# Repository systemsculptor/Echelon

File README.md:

# risc-v-research

### Features
Modularity, Ports, Periperials will be able to be swapped out. 

Cost efficient solution for students or professionals looking for a laptop 

Reparibility is very straightforward and simple. 

Upgradability is supported for these devices for lifetime.

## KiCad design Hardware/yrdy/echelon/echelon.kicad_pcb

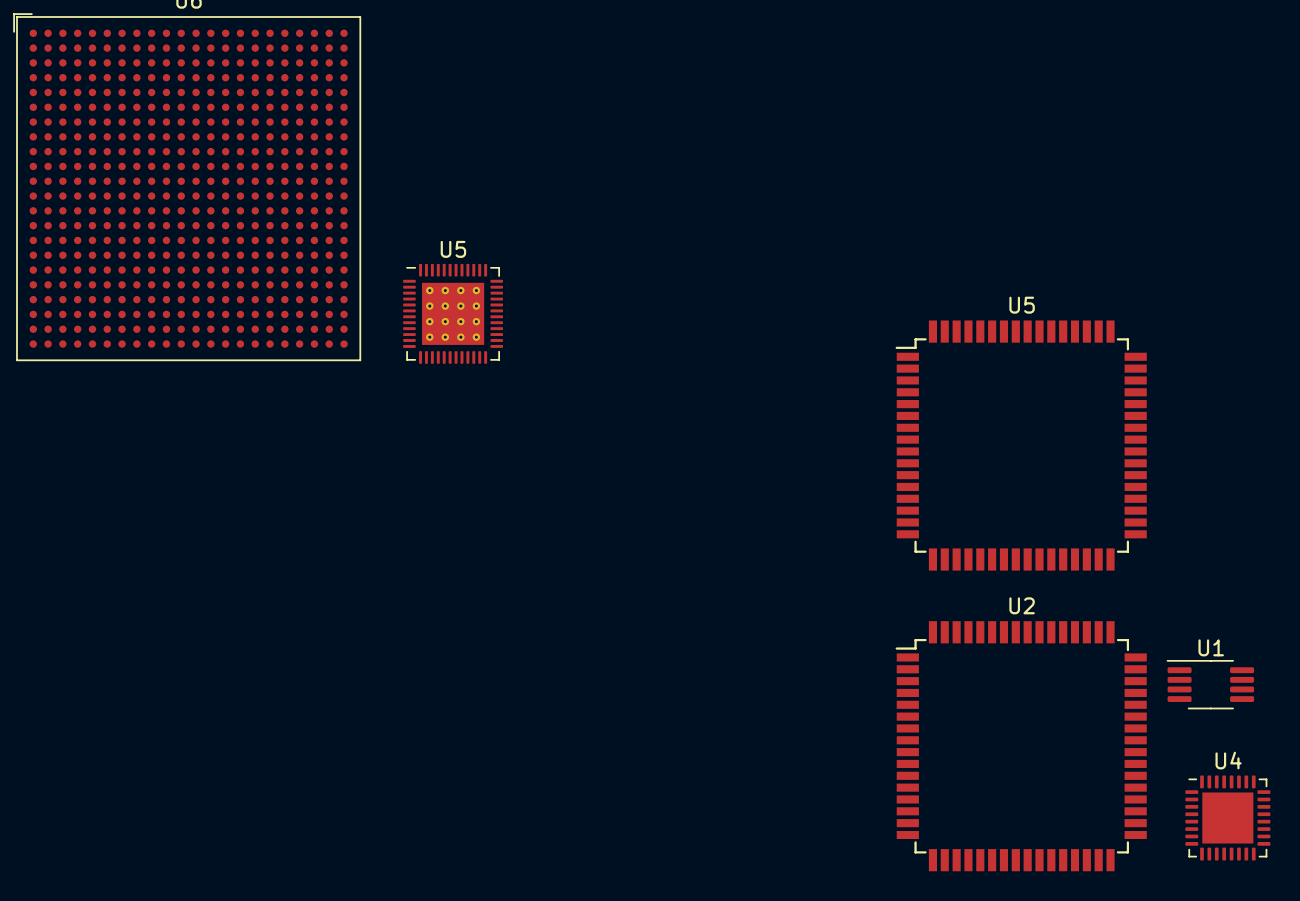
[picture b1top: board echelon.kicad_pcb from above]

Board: 2 copper layers, 6 parts (0 on the bottom side), 37 nets, no tracks yet.

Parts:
U1: ADC081C021CIMM; MSOP-8_3x3mm_P0.65mm
U2, U5#2: ATxmega384D3-A; TQFP-64_14x14mm_P0.8mm
U4: ESP8266EX; QFN-32-1EP_5x5mm_P0.5mm_EP3.45x3.45mm
U5: FE310-G002; QFN-48-1EP_6x6mm_P0.4mm_EP4.2x4.2mm_ThermalVias
U6: FU540-C000; BGA-484_23.0x23.0mm_Layout22x22_P1.0mm

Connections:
GND: U1.7 (GND), U2.14 (GND), U2.24 (GND), U2.34 (GND), U2.44 (GND), U2.52 (GND), U2.60 (GND), U4.33 (GND)
unnamed: U2.15 (VCC), U2.25 (VCC), U2.35 (VCC), U2.45 (VCC), U2.53 (VCC)
unnamed: U5#2.14 (GND), U5#2.24 (GND), U5#2.34 (GND), U5#2.44 (GND), U5#2.52 (GND), U5#2.60 (GND)
unnamed: U5.11 (IVDD), U5.32 (IVDD), U5.47 (IVDD)
unnamed: U5#2.15 (VCC), U5#2.25 (VCC), U5#2.35 (VCC), U5#2.45 (VCC), U5#2.53 (VCC)
unnamed: U5.6 (VDD), U5.30 (VDD), U5.46 (VDD)
unnamed: U6.V19 (CL_0_B2C_D_15), U6.Y16 (CL_0_B2C_D_0), U6.Y21 (CL_0_B2C_D_31)
unnamed: U6.L17 (CL_0_C2B_D_31), U6.M17 (CL_0_C2B_D_15), U6.T19 (CL_0_C2B_D_0)
unnamed: U6.M4 (DDR_MEM_BANK[0]), U6.M5 (DDR_MEM_BANK[2]), U6.V3 (DDR_MEM_ADDR[15])
unnamed: U6.K5 (DDR_MEM_CLK), U6.L5 (DDR_MEM_CLK_N)
unnamed: U6.T4 (DDR_MEM_D[34]), U6.T5 (DDR_MEM_DM[4]), U6.U5 (DDR_MEM_D[39])
unnamed: U6.C1 (DDR_MEM_D[4]), U6.D2 (DDR_MEM_D[0]), U6.E2 (DDR_MEM_D[3]), U6.G3 (DDR_MEM_D[7])
unnamed: U6.F5 (DDR_MEM_D[10]), U6.H4 (DDR_MEM_D[8]), U6.J4 (DDR_MEM_D[15])
unnamed: U6.B4 (DDR_MEM_D[16]), U6.B6 (DDR_MEM_D[23])
unnamed: U6.C3 (DDR_MEM_D[27]), U6.C4 (DDR_MEM_D[24]), U6.C7 (DDR_MEM_D[31]), U6.E6 (DDR_MEM_D[28])
unnamed: U6.AA4 (DDR_MEM_D[47]), U6.V5 (DDR_MEM_D[40]), U6.Y3 (DDR_MEM_D[42])
unnamed: U6.W8 (DDR_MEM_D[51]), U6.W9 (DDR_MEM_D[55]), U6.Y12 (DDR_MEM_D[48])
unnamed: U6.AA11 (DDR_MEM_D[63]), U6.AA13 (DDR_MEM_D[56])
unnamed: U6.J5 (DDR_MEM_ECC_DM), U6.L3 (DDR_MEM_ECC_D[7])
unnamed: U6.D8 (DDR_RSVD1), U6.E8 (DDR_RSVD0), U6.F9 (DDR_RSVD3)
unnamed: U6.A8 (GEMGXL_0_RXD_5), U6.A12 (GEMGXL_0_RXD_0), U6.C9 (GEMGXL_0_RXD_6), U6.E9 (GEMGXL_0_RXD_7)
unnamed: U6.B12 (GEMGXL_0_TXD_0), U6.C10 (GEMGXL_0_TXD_4), U6.D9 (GEMGXL_0_TXD_7)
unnamed: U6.C20 (GPIO_0_P_7), U6.F17 (GPIO_0_P_0), U6.G17 (GPIO_0_P_15)
unnamed: U6.F19 (PWM_1_P_3), U6.G19 (PWM_0_P_0), U6.G20 (PWM_0_P_3)
unnamed: U6.H20 (QSPI_0_DQ_3), U6.H21 (QSPI_0_DQ_0)
unnamed: U6.H19 (QSPI_1_CS_2), U6.J20 (QSPI_1_CS_3), U6.K17 (QSPI_1_CS_0)
unnamed: U6.G22 (QSPI_1_DQ_0), U6.J17 (QSPI_1_DQ_3), U6.J18 (QSPI_1_DQ_1)
unnamed: U6.A19 (MSEL_MSEL_0), U6.B19 (MSEL_MSEL_3)
unnamed: U6.D16 (PRCI_RSVD3), U6.E16 (PRCI_RSVD9)
unnamed: U6.D17 (PRCI_RSVD10), U6.E14 (PRCI_RSVD12)
unnamed: U6.C14 (PRCI_RSVD15), U6.F14 (PRCI_RSVD13)
unnamed: U6.L9 (DDR_VDDPLL), U6.M9 (DDR_VDDPLL)
unnamed: U6.G7 (DDR_VDDQ), U6.H6 (DDR_VDDQ), U6.J7 (DDR_VDDQ), U6.K6 (DDR_VDDQ), U6.L7 (DDR_VDDQ), U6.M6 (DDR_VDDQ), U6.N7 (DDR_VDDQ), U6.P6 (DDR_VDDQ), U6.R7 (DDR_VDDQ), U6.T6 (DDR_VDDQ)
unnamed: U6.K16 (IVDD), U6.L16 (IVDD), U6.M16 (IVDD), U6.N16 (IVDD)
unnamed: U6.K15 (IVSS), U6.L15 (IVSS), U6.M15 (IVSS), U6.N15 (IVSS)
unnamed: U6.AA17 (VDD), U6.B9 (VDD), U6.B14 (VDD), U6.B18 (VDD), U6.E3 (VDD), U6.E21 (VDD), U6.G9 (VDD), U6.G11 (VDD), U6.G15 (VDD), U6.H8 (VDD), U6.H10 (VDD), U6.H12 (VDD), U6.H14 (VDD), U6.H16 (VDD), U6.J9 (VDD), U6.J15 (VDD), U6.K8 (VDD), U6.K10 (VDD), U6.K21 (VDD), U6.L11 (VDD), U6.L13 (VDD), U6.M8 (VDD), U6.M10 (VDD), U6.M12 (VDD), U6.M14 (VDD), U6.N9 (VDD), U6.N11 (VDD), U6.N13 (VDD), U6.P2 (VDD), U6.P8 (VDD), U6.P10 (VDD), U6.P12 (VDD), U6.P14 (VDD), U6.P16 (VDD), U6.P21 (VDD), U6.R9 (VDD), U6.R11 (VDD), U6.R13 (VDD), U6.R15 (VDD), U6.T8 (VDD), U6.T10 (VDD), U6.T12 (VDD), U6.T14 (VDD), U6.T16 (VDD), U6.U9 (VDD), U6.U11 (VDD), U6.U13 (VDD), U6.U15 (VDD), U6.V6 (VDD), U6.V8 (VDD), U6.V10 (VDD), U6.V12 (VDD), U6.V14 (VDD), U6.V21 (VDD)
unnamed: U6.A1 (VSS), U6.A2 (VSS), U6.A3 (VSS), U6.A9 (VSS), U6.A14 (VSS), U6.A18 (VSS), U6.A22 (VSS), U6.AA2 (VSS), U6.AB1 (VSS), U6.AB4 (VSS), U6.AB7 (VSS), U6.AB10 (VSS), U6.AB13 (VSS), U6.AB17 (VSS), U6.AB22 (VSS), U6.D1 (VSS), U6.D12 (VSS), U6.E4 (VSS), U6.E22 (VSS), U6.F7 (VSS), U6.G2 (VSS), U6.G6 (VSS), U6.G8 (VSS), U6.G10 (VSS), U6.G12 (VSS), U6.G16 (VSS), U6.H7 (VSS), U6.H9 (VSS), U6.H15 (VSS), U6.J1 (VSS), U6.J6 (VSS), U6.J8 (VSS), U6.J10 (VSS), U6.J16 (VSS), U6.J22 (VSS), U6.K7 (VSS), U6.K9 (VSS), U6.K11 (VSS), U6.L6 (VSS), U6.L8 (VSS), U6.L10 (VSS), U6.L12 (VSS), U6.L14 (VSS), U6.M7 (VSS), U6.M11 (VSS), U6.M13 (VSS), U6.N6 (VSS), U6.N8 (VSS), U6.N10 (VSS), U6.N12 (VSS), U6.N14 (VSS), U6.P1 (VSS), U6.P7 (VSS), U6.P9 (VSS), U6.P11 (VSS), U6.P13 (VSS), U6.P15 (VSS), U6.P22 (VSS), U6.R6 (VSS), U6.R8 (VSS), U6.R10 (VSS), U6.R12 (VSS), U6.R14 (VSS), U6.R16 (VSS), U6.T7 (VSS), U6.T9 (VSS), U6.T11 (VSS), U6.T13 (VSS), U6.T15 (VSS), U6.T17 (VSS), U6.U6 (VSS), U6.U8 (VSS), U6.U10 (VSS), U6.U12 (VSS), U6.U14 (VSS), U6.U16 (VSS), U6.V1 (VSS), U6.V7 (VSS), U6.V9 (VSS), U6.V11 (VSS), U6.V13 (VSS), U6.V15 (VSS), U6.V22 (VSS)

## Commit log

2023-08-03 Create TODO-LIST
2023-08-22 Create t
2023-11-06 naming and reorganization
2023-11-08 fully finished length width
2024-02-09 eess
2024-02-29 llll
2024-04-20 dddd
    dd
2024-04-22 cee
    c
